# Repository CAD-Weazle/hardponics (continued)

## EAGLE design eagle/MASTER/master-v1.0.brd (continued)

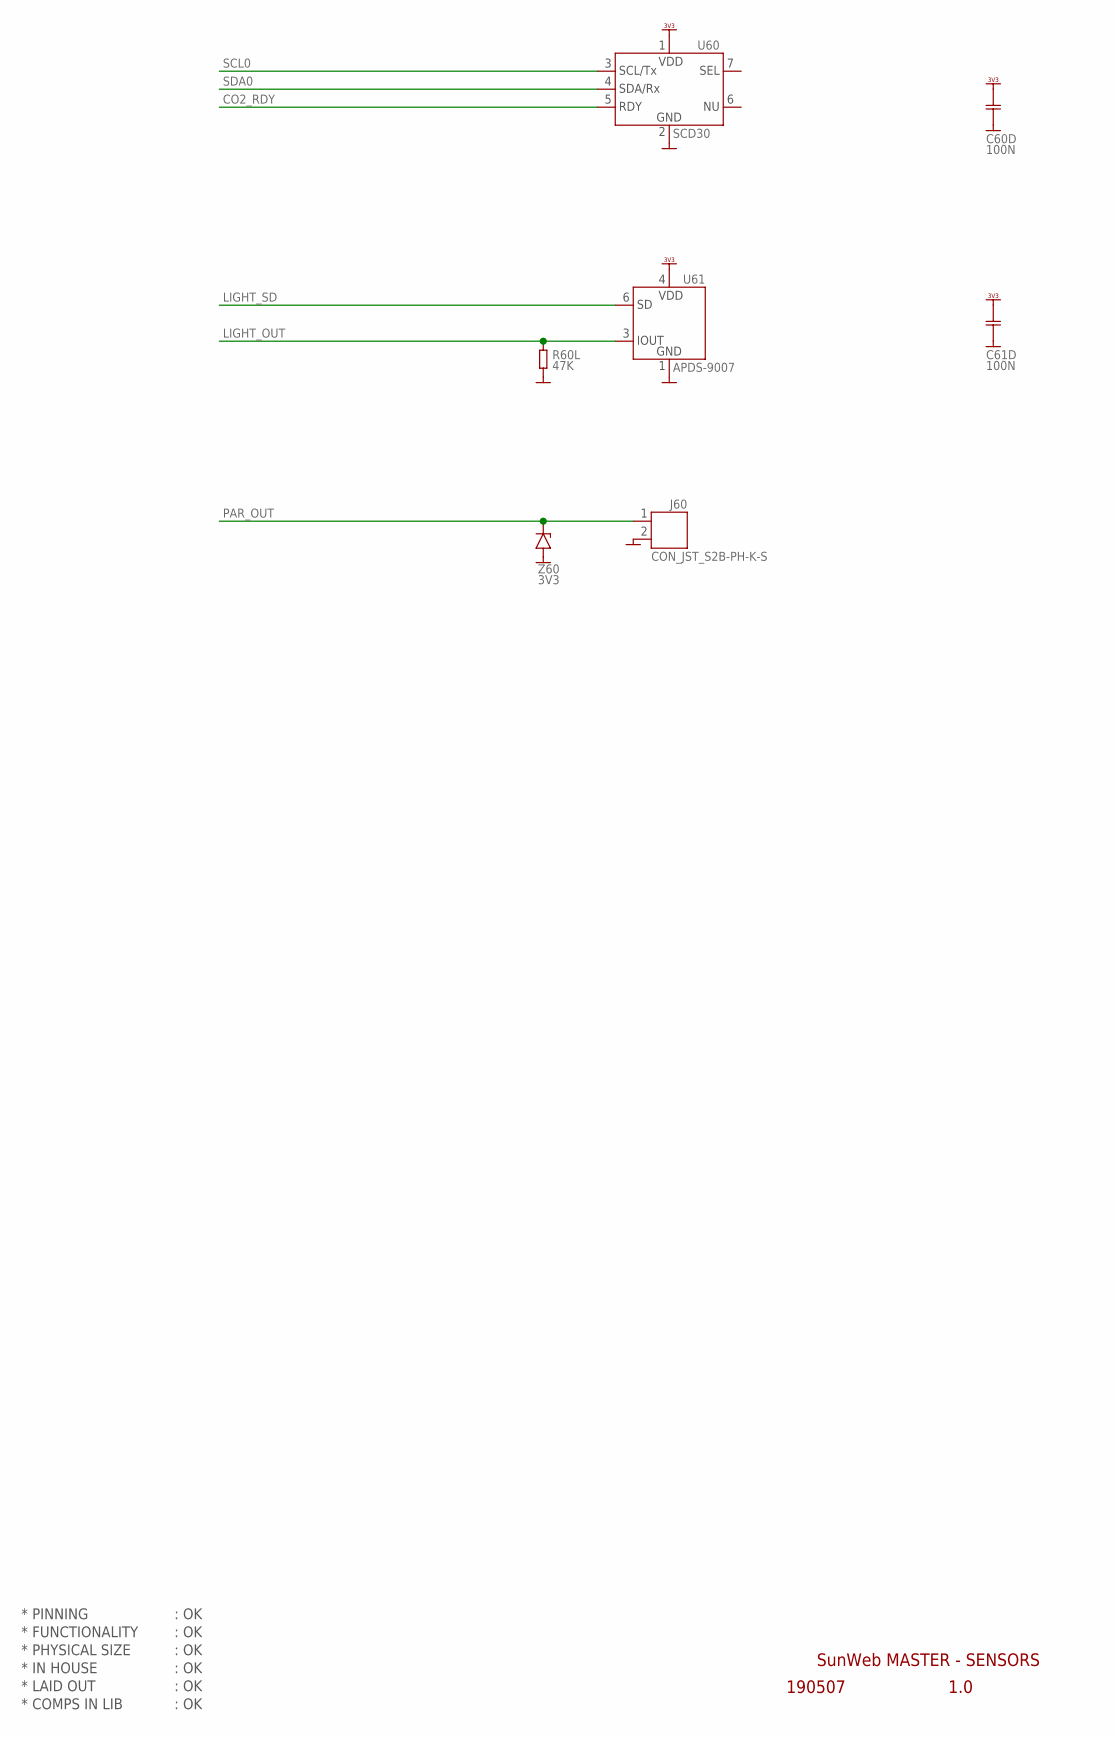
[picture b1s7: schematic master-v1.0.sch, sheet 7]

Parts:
C60D, C61D: 100N; CAP0603
J60: CON_JST_S2B-PH-K-S
R60L: 47K; RES0603
U60: SCD30
U61: APDS-9007
Z60: 3V3; ZENER_SOD80

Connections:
CO2_RDY: U60.5 (5.RDY); also elsewhere on the board
GND: C60D.2, C61D.2, J60.2, R60L.2, U60.2 (2.GND), U61.1 (1.GND), Z60.1 (+); also elsewhere on the board
LIGHT_OUT: R60L.1, U61.3 (3.IOUT); also elsewhere on the board
LIGHT_SD: U61.6 (6.SD); also elsewhere on the board
PAR_OUT: J60.1, Z60.2 (-); also elsewhere on the board
SCL0: U60.3 (3.SCL); also elsewhere on the board
SDA0: U60.4 (4.SDA); also elsewhere on the board
VDD_3V3: C60D.1, C61D.1, U60.1 (1.VDD), U61.4 (4.VDD); also elsewhere on the board

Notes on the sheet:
* PINNING
* FUNCTIONALITY
* PHYSICAL SIZE
* LAID OUT
* COMPS IN LIB
* IN HOUSE
1.0
SunWeb MASTER - SENSORS
190507
: OK

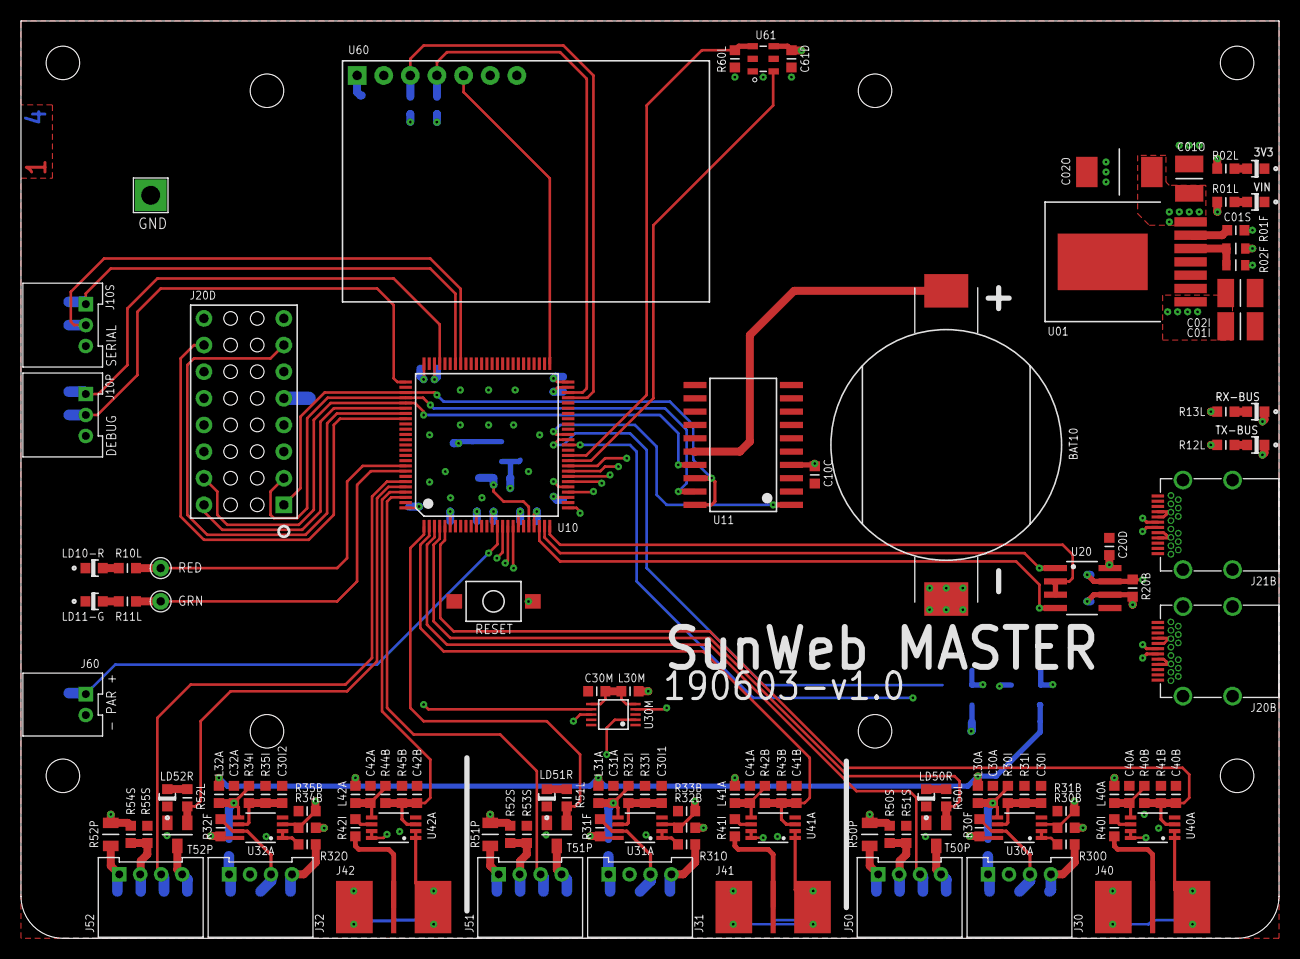
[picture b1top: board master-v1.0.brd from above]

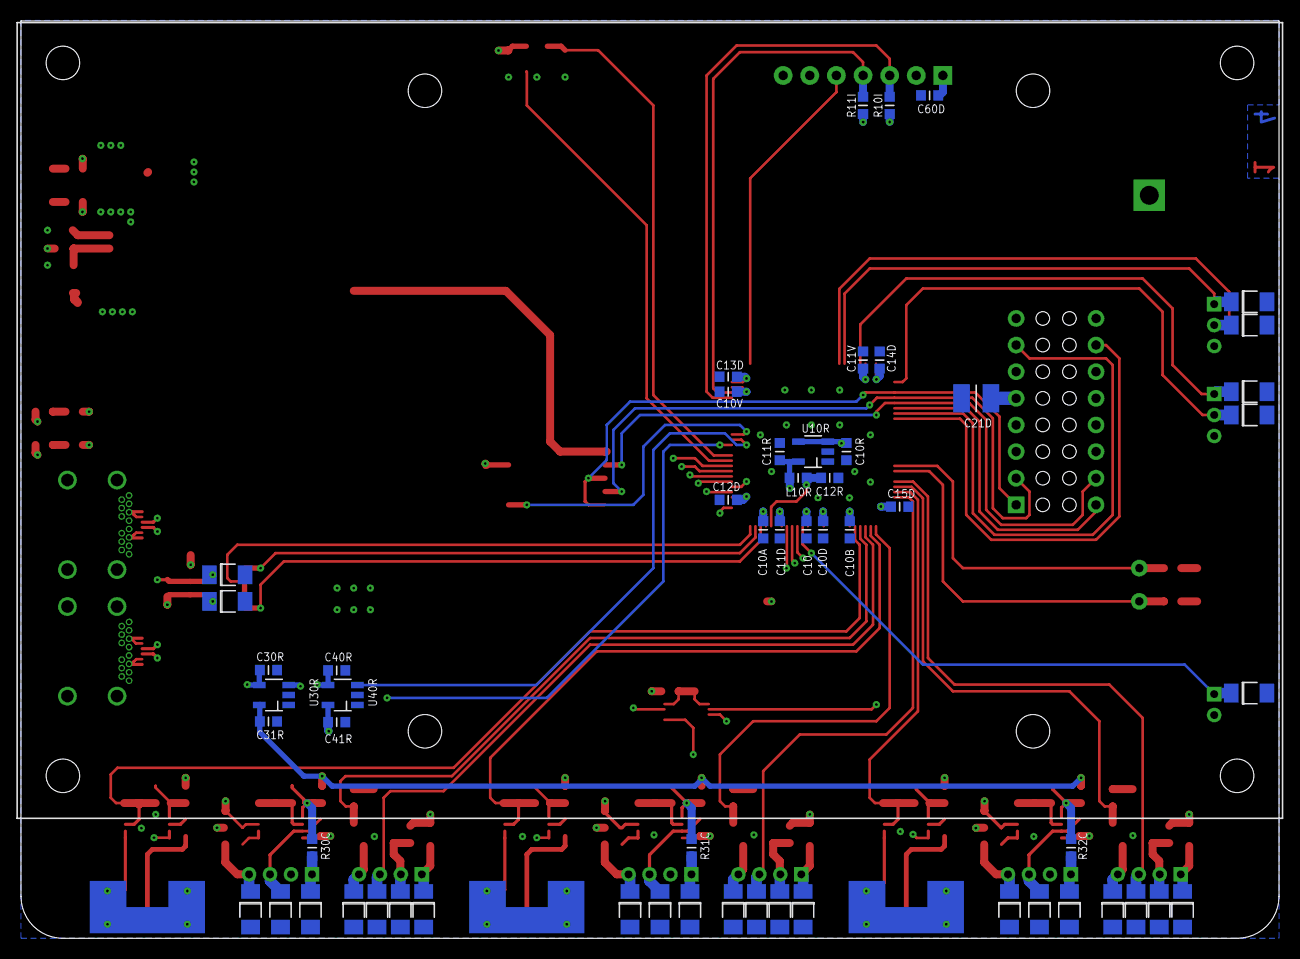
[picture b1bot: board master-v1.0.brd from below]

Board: 4 copper layers, 120.0 x 87.5 mm, 183 parts (58 on the bottom side), 107 nets.

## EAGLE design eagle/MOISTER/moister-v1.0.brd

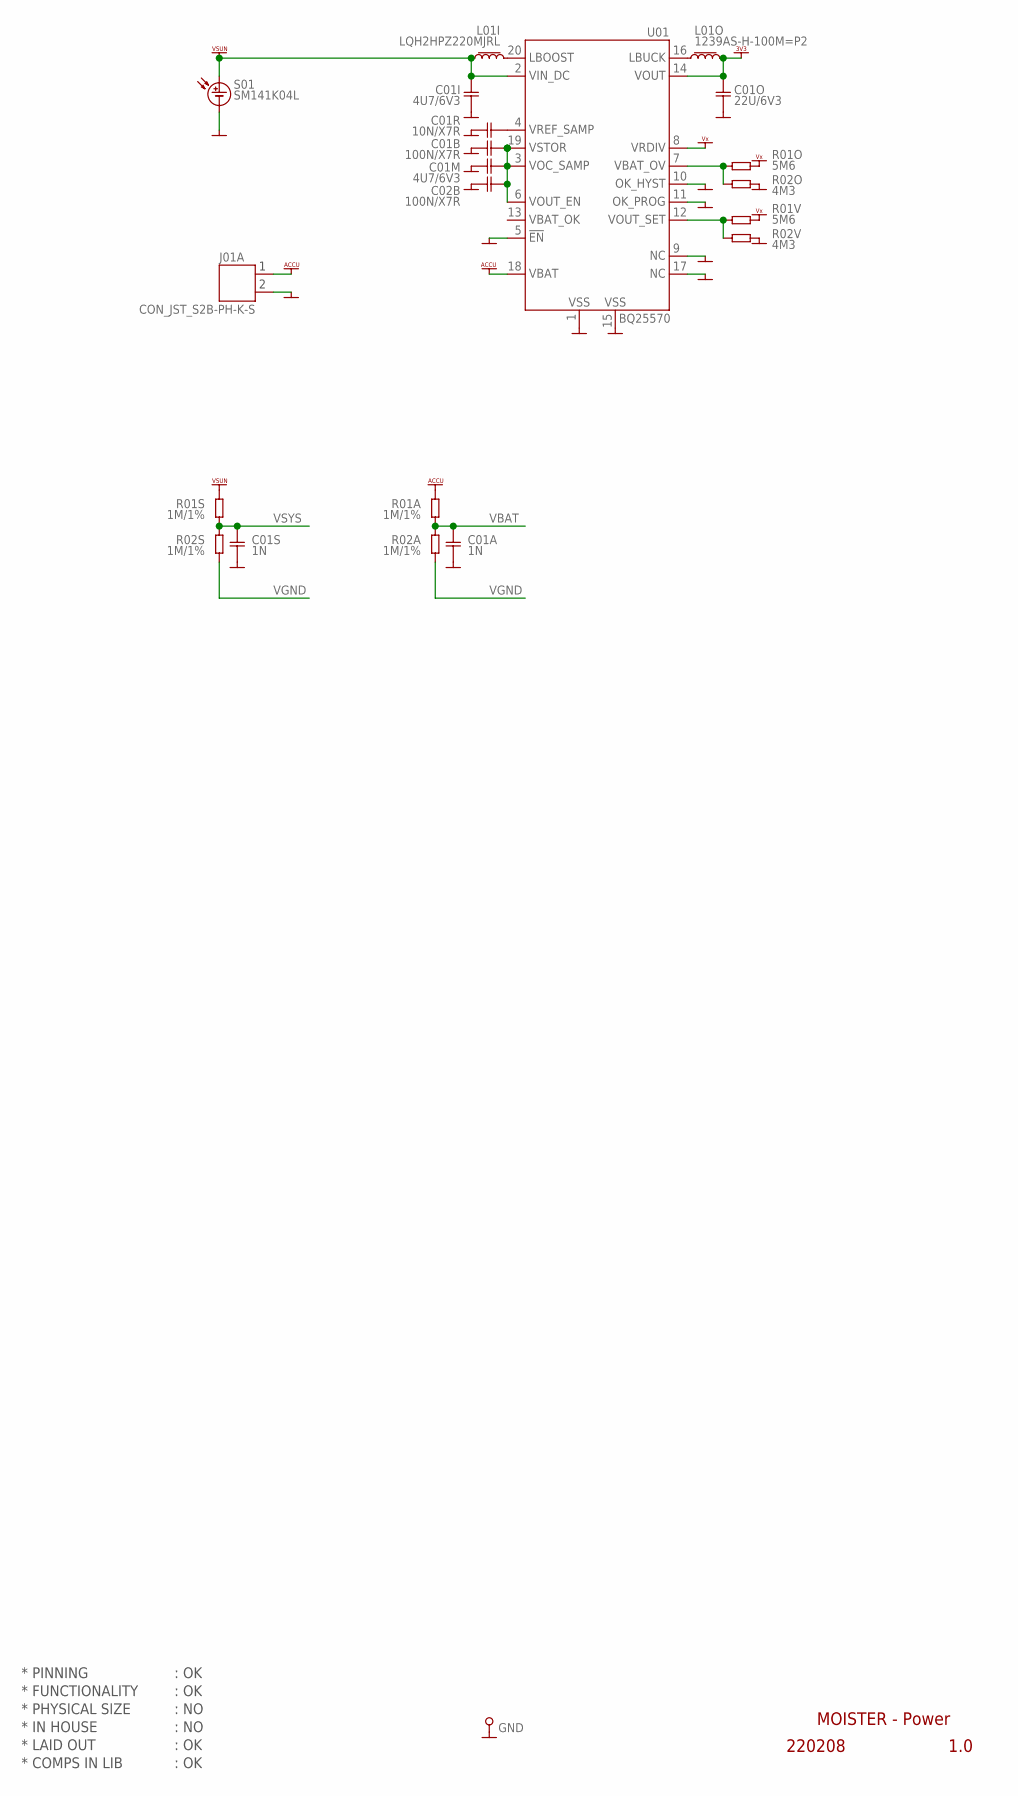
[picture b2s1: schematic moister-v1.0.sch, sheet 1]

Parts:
C01A, C01S: 1N; CAP0402
C01B, C02B: 100N/X7R; CAP0402
C01I, C01M: 4U7/6V3; CAP0402
C01O: 22U/6V3; CAP0402
C01R: 10N/X7R; CAP0402
GND: PIN_TEST; HOLE_PTH_0.8MM
J01A: CON_JST_S2B-PH-K-S
L01I: LQH2HPZ220MJRL; L_1008
L01O: 1239AS-H-100M=P2; L_1008
R01A, R01S, R02A, R02S: 1M/1%; RES0402
R01O, R01V: 5M6; RES0402
R02O, R02V: 4M3; RES0402
S01: SM141K04L
U01: BQ25570; VQFN20

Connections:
ACCU: J01A.1, R01A.2, U01.18 (18.VBAT)
GND: C01A.2, C01B.2, C01I.2, C01M.2, C01O.2, C01R.2, C01S.2, C02B.2, GND.1, J01A.2, R02O.2, R02V.2, S01.-, U01.1 (1.VSS), U01.5 (5.!EN), U01.9 (9.NC), U01.10 (10.OK_HYST), U01.11 (11.OK_PROG), U01.15 (15.VSS), U01.17 (17.NC), U01.TP (15.VSS), U01.V1 (15.VSS), U01.V2 (15.VSS), U01.V3 (15.VSS), U01.V4 (15.VSS); also elsewhere on the board
unnamed: C01R.1, U01.4 (4.VREF_SAMP)
unnamed: L01I.2, U01.20 (20.LBOOST)
unnamed: L01O.1, U01.16 (16.LBUCK)
VBAT: C01A.1, R01A.1, R02A.2; also elsewhere on the board
VBAT_OV: R01O.2, R02O.1, U01.7 (7.VBAT_OV)
VDD_3V3: C01O.1, L01O.2, U01.14 (14.VOUT); also elsewhere on the board
VGND: R02A.1, R02S.1; also elsewhere on the board
VOUT_SET: R01V.2, R02V.1, U01.12 (12.VOUT_SET)
VSTOR: C01B.1, C01M.1, C02B.1, U01.3 (3.VOC_SAMP), U01.6 (6.VOUT_EN), U01.19 (19.VSTOR)
VSUN: C01I.1, L01I.1, R01S.2, S01.+, U01.2 (2.VIN_DC)
VSYS: C01S.1, R01S.1, R02S.2; also elsewhere on the board
VX: R01O.1, R01V.1, U01.8 (8.VRDIV)

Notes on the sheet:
* PINNING
* FUNCTIONALITY
* PHYSICAL SIZE
* LAID OUT
* COMPS IN LIB
* IN HOUSE
MOISTER - Power
220208
1.0
: OK
: NO

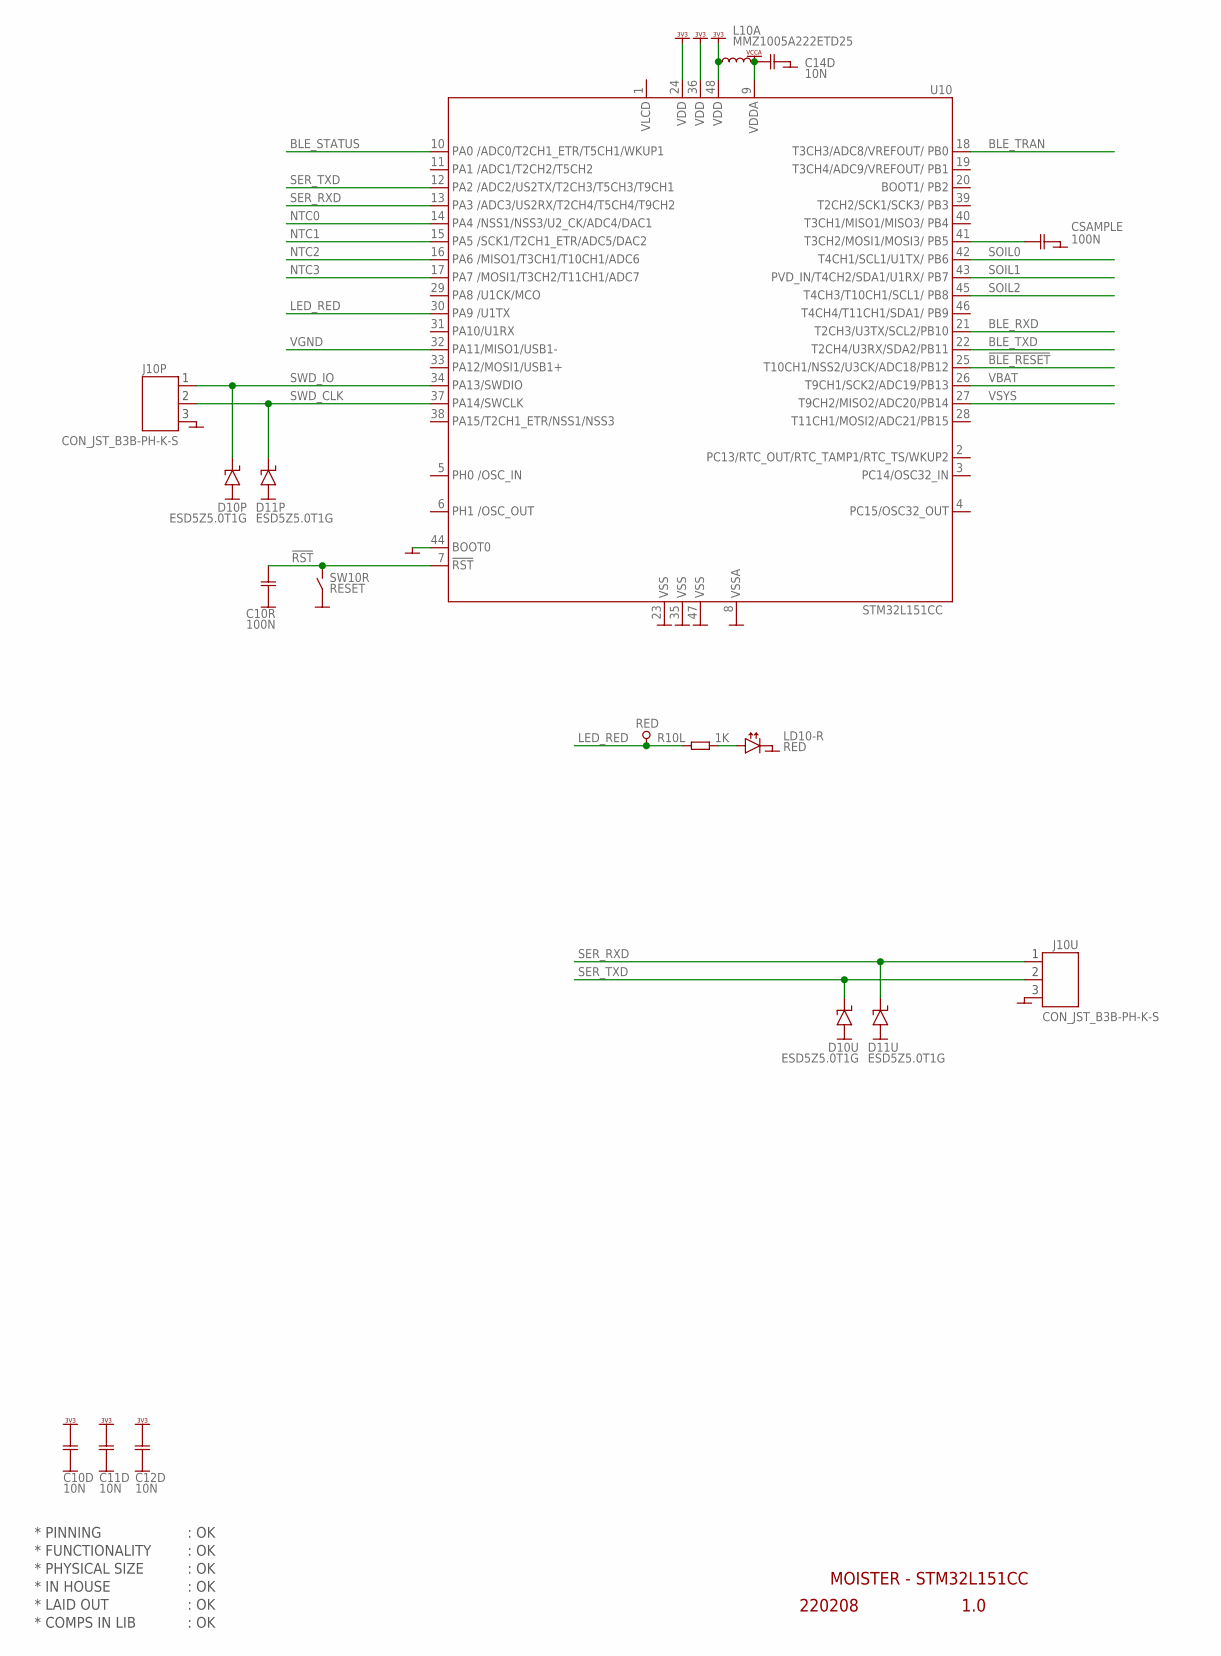
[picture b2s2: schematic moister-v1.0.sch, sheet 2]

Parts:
C10D, C11D, C12D, C14D: 10N; CAP0402
C10R: 100N; CAP0402
CSAMPLE: 100N; CAP0603
D10P, D10U, D11P, D11U: ESD5Z5.0T1G; DIODE_SOD523
J10P, J10U: CON_JST_B3B-PH-K-S
L10A: MMZ1005A222ETD25; L_0402
LD10-R: RED; LED_SMD_0402
R10L: 1K; RES0402
RED: PIN_TEST_0.6MM; HOLE_PTH_0.6MM
SW10R: RESET; SWITCH_SMD_PBUTTON_2P
U10: STM32L151CC; LQFP48

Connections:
!BLE_RESET: U10.25 (25.PB12); also elsewhere on the board
!RST: C10R.1, SW10R.1 (1-2), U10.7 (7.!RST)
BLE_RXD: U10.21 (21.PB10); also elsewhere on the board
BLE_STATUS: U10.10 (10.PA0); also elsewhere on the board
BLE_TRAN: U10.18 (18.PB0); also elsewhere on the board
BLE_TXD: U10.22 (22.PB11); also elsewhere on the board
CSAMPLE: CSAMPLE.1, U10.41 (41.PB5)
GND: C10D.2, C10R.2, C11D.2, C12D.2, C14D.2, CSAMPLE.2, D10P.A, D10U.A, D11P.A, D11U.A, J10P.3, J10U.3, LD10-R.C, SW10R.2 (3-4), U10.8 (8.GND), U10.23 (23.GND), U10.35 (35.GND), U10.44 (44.BOOT0), U10.47 (47.GND); also elsewhere on the board
LED_RED: R10L.1, RED.1, U10.30 (30.PA9)
unnamed: LD10-R.A, R10L.2
NTC0: U10.14 (14.PA4); also elsewhere on the board
NTC1: U10.15 (15.PA5); also elsewhere on the board
NTC2: U10.16 (16.PA6); also elsewhere on the board
NTC3: U10.17 (17.PA7); also elsewhere on the board
SER_RXD: D11U.C, J10U.1, U10.13 (13.PA3)
SER_TXD: D10U.C, J10U.2, U10.12 (12.PA2)
SOIL0: U10.42 (42.PB6); also elsewhere on the board
SOIL1: U10.43 (43.PB7); also elsewhere on the board
SOIL2: U10.45 (45.PB8); also elsewhere on the board
SWD_CLK: D11P.C, J10P.2, U10.37 (37.PA14)
SWD_IO: D10P.C, J10P.1, U10.34 (34.PA13)
VBAT: U10.26 (26.PB13); also elsewhere on the board
VCCA: C14D.1, L10A.2, U10.9 (9.VDD); also elsewhere on the board
VDD_3V3: C10D.1, C11D.1, C12D.1, L10A.1, U10.24 (24.VDD), U10.36 (36.VDD), U10.48 (48.VDD); also elsewhere on the board
VGND: U10.32 (32.PA11); also elsewhere on the board
VSYS: U10.27 (27.PB14); also elsewhere on the board

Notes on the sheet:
* PINNING
* FUNCTIONALITY
* PHYSICAL SIZE
* LAID OUT
* COMPS IN LIB
* IN HOUSE
: OK
MOISTER - STM32L151CC
220208
1.0

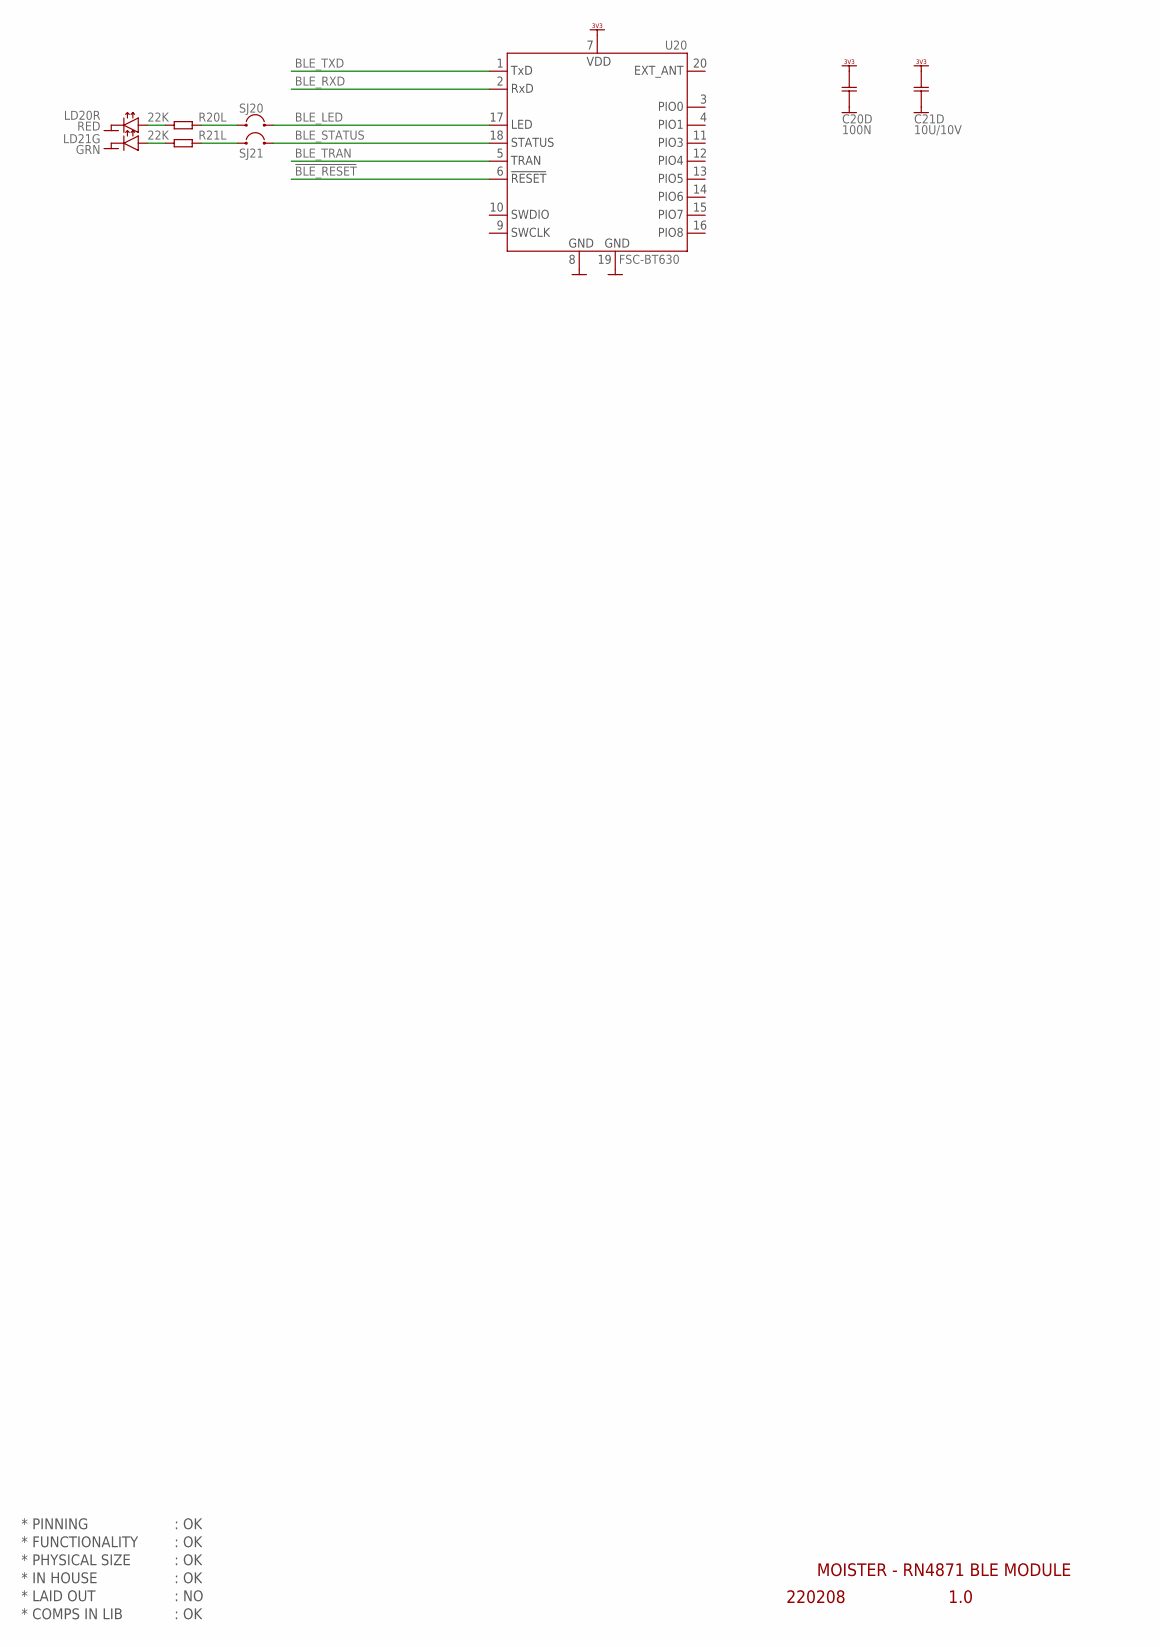
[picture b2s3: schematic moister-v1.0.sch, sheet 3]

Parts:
C20D: 100N; CAP0402
C21D: 10U/10V; CAP0402
LD20R: RED; LED_SMD_0402
LD21G: GRN; LED_SMD_0402
R20L, R21L: 22K; RES0402
SJ20, SJ21: SJ2SJ2-S; SJ2-S
U20: FSC-BT630

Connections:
!BLE_RESET: U20.6 (6.!RESET); also elsewhere on the board
BLE_LED: SJ20.2, U20.17 (17.LED)
BLE_RXD: U20.2 (2.RXD); also elsewhere on the board
BLE_STATUS: SJ21.2, U20.18 (18.STATUS); also elsewhere on the board
BLE_TRAN: U20.5 (5.TRAN); also elsewhere on the board
BLE_TXD: U20.1 (1.TXD); also elsewhere on the board
GND: C20D.2, C21D.2, LD20R.C, LD21G.C, U20.8 (8.GND), U20.19 (19.GND); also elsewhere on the board
unnamed: LD20R.A, R20L.2
unnamed: R20L.1, SJ20.1
unnamed: R21L.1, SJ21.1
unnamed: LD21G.A, R21L.2
VDD_3V3: C20D.1, C21D.1, U20.7 (7.VDD); also elsewhere on the board

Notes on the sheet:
* PINNING
* FUNCTIONALITY
* PHYSICAL SIZE
* LAID OUT
* COMPS IN LIB
* IN HOUSE
1.0
MOISTER - RN4871 BLE MODULE
220208
: OK
: NO

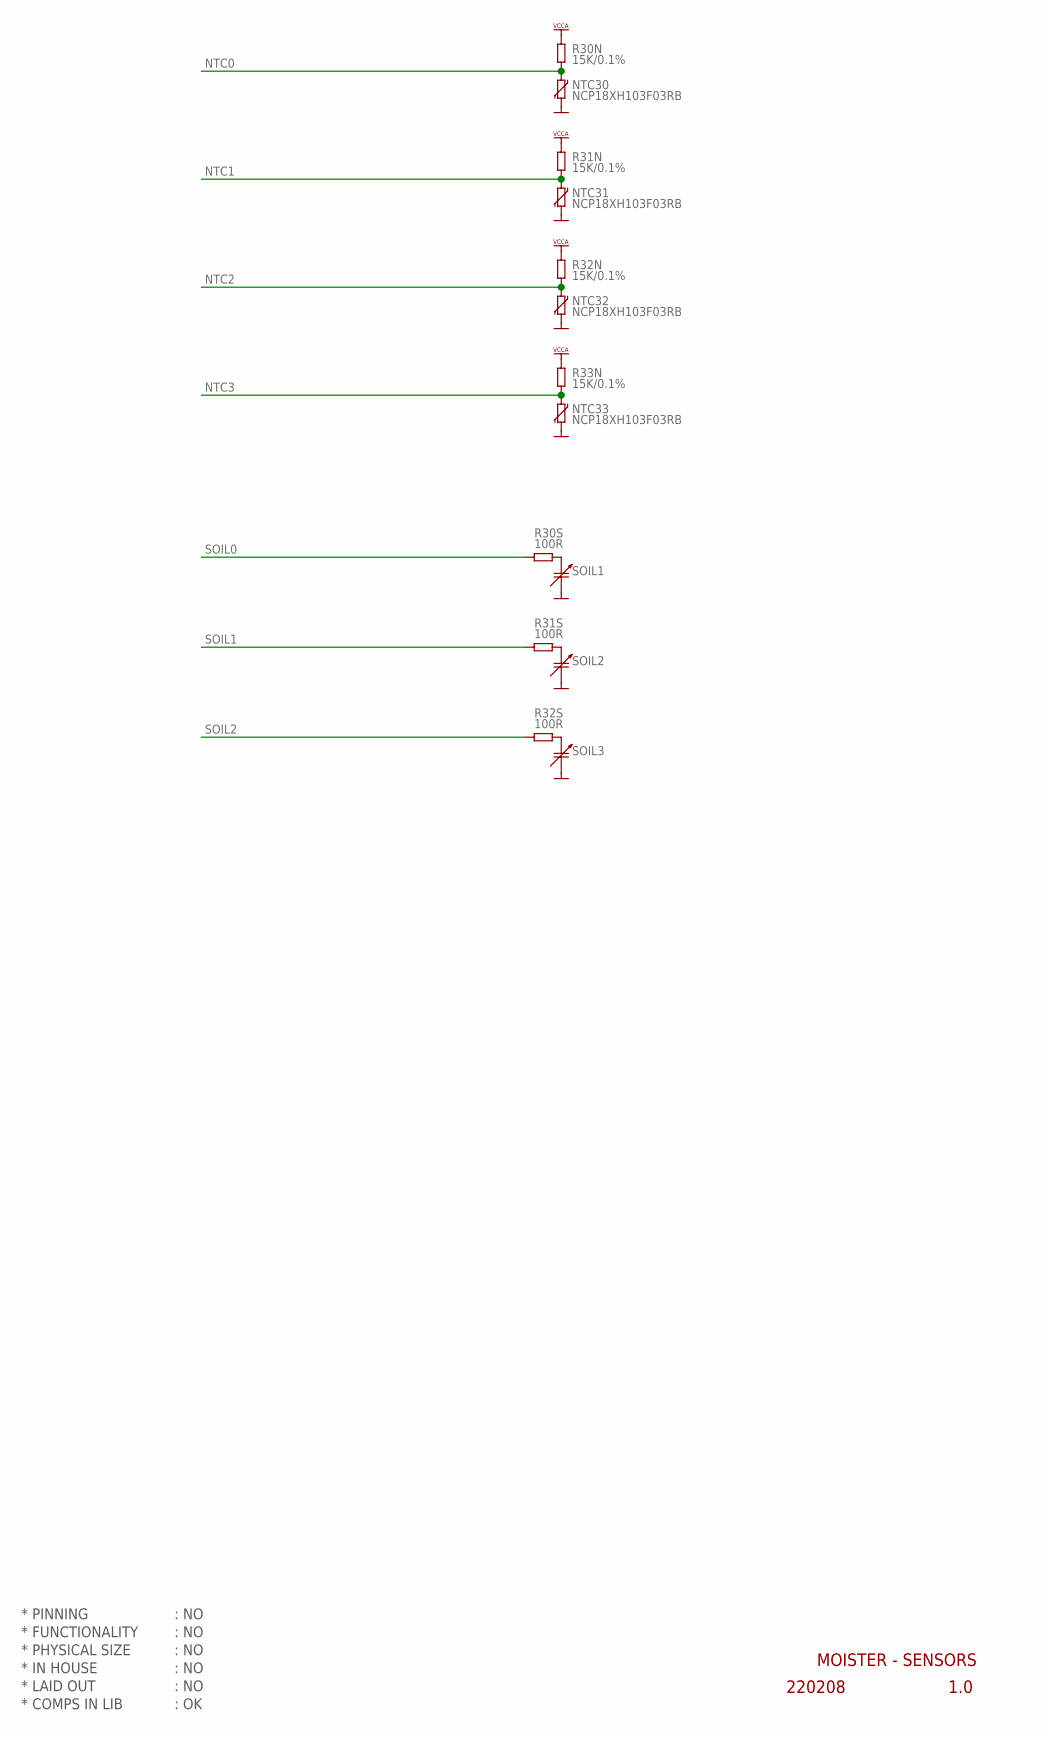
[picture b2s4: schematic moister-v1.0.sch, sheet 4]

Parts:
NTC30, NTC31, NTC32, NTC33: NCP18XH103F03RB; RES0603
R30N, R31N, R32N, R33N: 15K/0.1%; RES0402
R30S, R31S, R32S: 100R; RES0402
SOIL1, SOIL2, SOIL3: CAP_SOIL_SINGLE_2LAYER

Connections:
GND: NTC30.1, NTC31.1, NTC32.1, NTC33.1, SOIL1.2, SOIL2.2, SOIL3.2; also elsewhere on the board
unnamed: R30S.2, SOIL1.1
unnamed: R31S.2, SOIL2.1
unnamed: R32S.2, SOIL3.1
NTC0: NTC30.2, R30N.2; also elsewhere on the board
NTC1: NTC31.2, R31N.2; also elsewhere on the board
NTC2: NTC32.2, R32N.2; also elsewhere on the board
NTC3: NTC33.2, R33N.2; also elsewhere on the board
SOIL0: R30S.1; also elsewhere on the board
SOIL1: R31S.1; also elsewhere on the board
SOIL2: R32S.1; also elsewhere on the board
VCCA: R30N.1, R31N.1, R32N.1, R33N.1; also elsewhere on the board

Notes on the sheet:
* PINNING
* FUNCTIONALITY
* PHYSICAL SIZE
* LAID OUT
* COMPS IN LIB
* IN HOUSE
1.0
MOISTER - SENSORS
220208
: NO
: OK

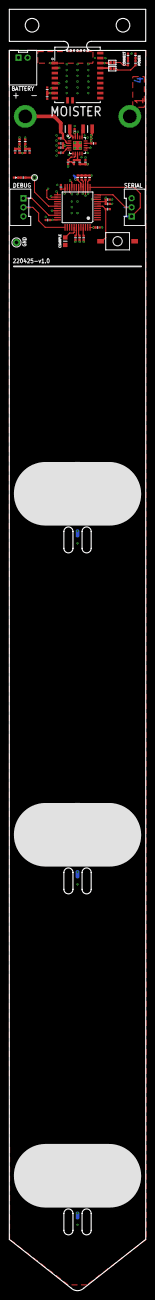
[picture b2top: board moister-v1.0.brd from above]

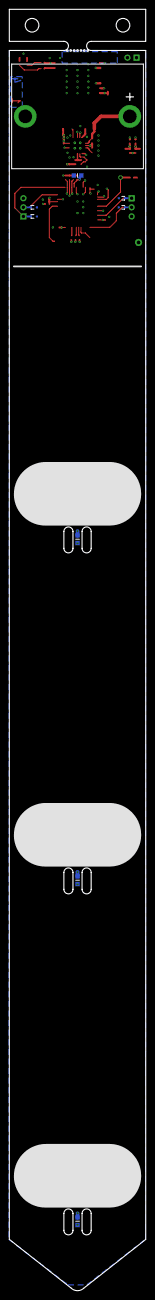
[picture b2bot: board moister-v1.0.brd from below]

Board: 4 copper layers, 30.0 x 281.8 mm, 66 parts (9 on the bottom side), 43 nets.

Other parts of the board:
U$45: EC_MOUSEBITES
U$46, U$47: EC_TOOL-REGISTRATION

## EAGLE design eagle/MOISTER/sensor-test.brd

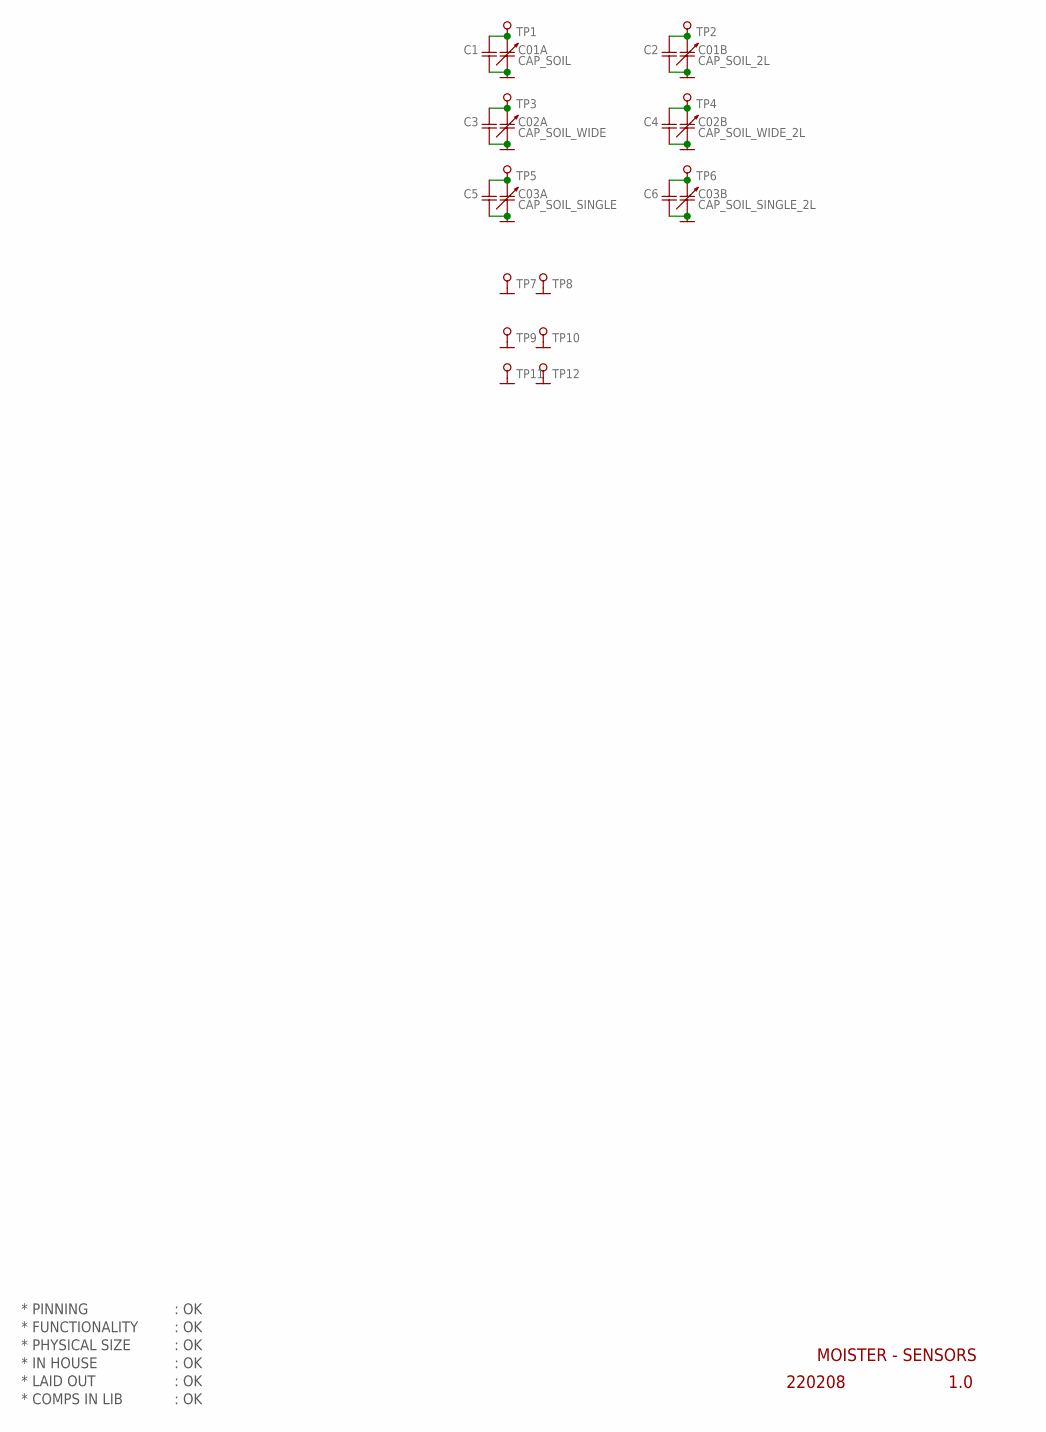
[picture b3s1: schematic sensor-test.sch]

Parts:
C1, C2, C3, C4, C5, C6: CAP0805
C01A: CAP_SOIL
C01B: CAP_SOIL_2L; CAP_SOIL_2LAYER
C02A: CAP_SOIL_WIDE
C02B: CAP_SOIL_WIDE_2L; CAP_SOIL_WIDE_2LAYER
C03A: CAP_SOIL_SINGLE
C03B: CAP_SOIL_SINGLE_2L; CAP_SOIL_SINGLE_2LAYER
TP1, TP2, TP3, TP4, TP5, TP6, TP7, TP8, TP9, TP10, TP11, TP12: PIN_TEST; HOLE_PTH_0.8MM

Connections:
GND: C1.2, C01A.2, C01B.2, C01B.P$1 (2), C2.2, C02A.2, C02B.2, C02B.P$1 (2), C3.2, C03A.2, C03B.2, C4.2, C5.2, C6.2, TP7.1, TP8.1, TP9.1, TP10.1, TP11.1, TP12.1
unnamed: C1.1, C01A.1, TP1.1
unnamed: C01B.1, C2.1, TP2.1
unnamed: C02A.1, C3.1, TP3.1
unnamed: C02B.1, C4.1, TP4.1
unnamed: C03A.1, C5.1, TP5.1
unnamed: C03B.1, C6.1, TP6.1

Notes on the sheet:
* PINNING
* FUNCTIONALITY
* PHYSICAL SIZE
* LAID OUT
* COMPS IN LIB
* IN HOUSE
1.0
MOISTER - SENSORS
220208
: OK

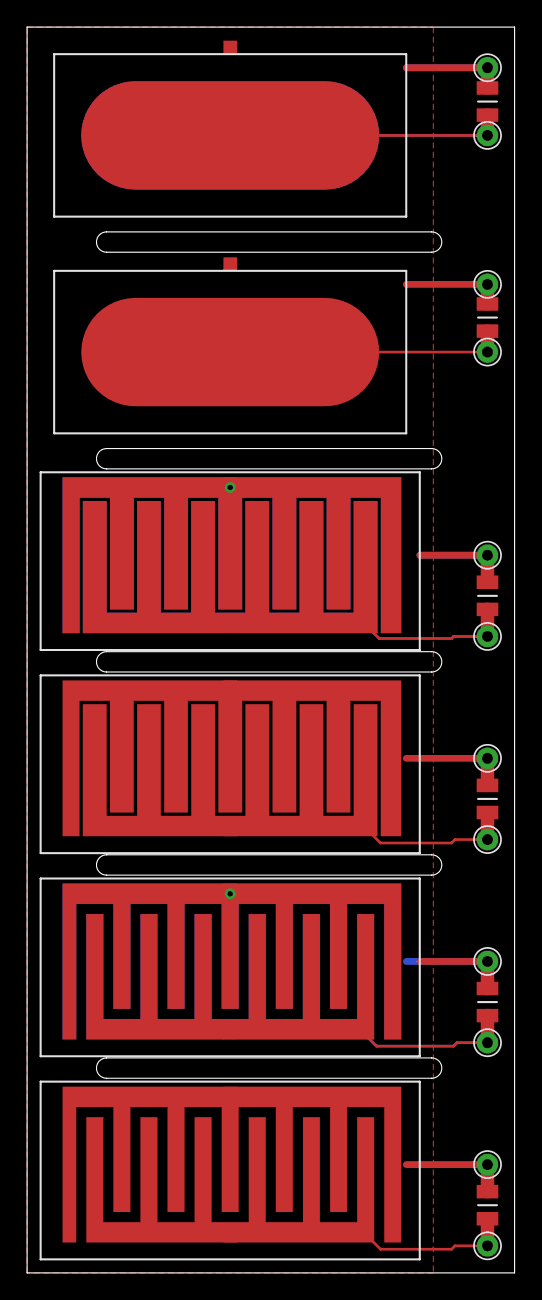
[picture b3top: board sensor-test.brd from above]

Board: 4 copper layers, 36.0 x 92.0 mm, 24 parts (0 on the bottom side), 7 nets.

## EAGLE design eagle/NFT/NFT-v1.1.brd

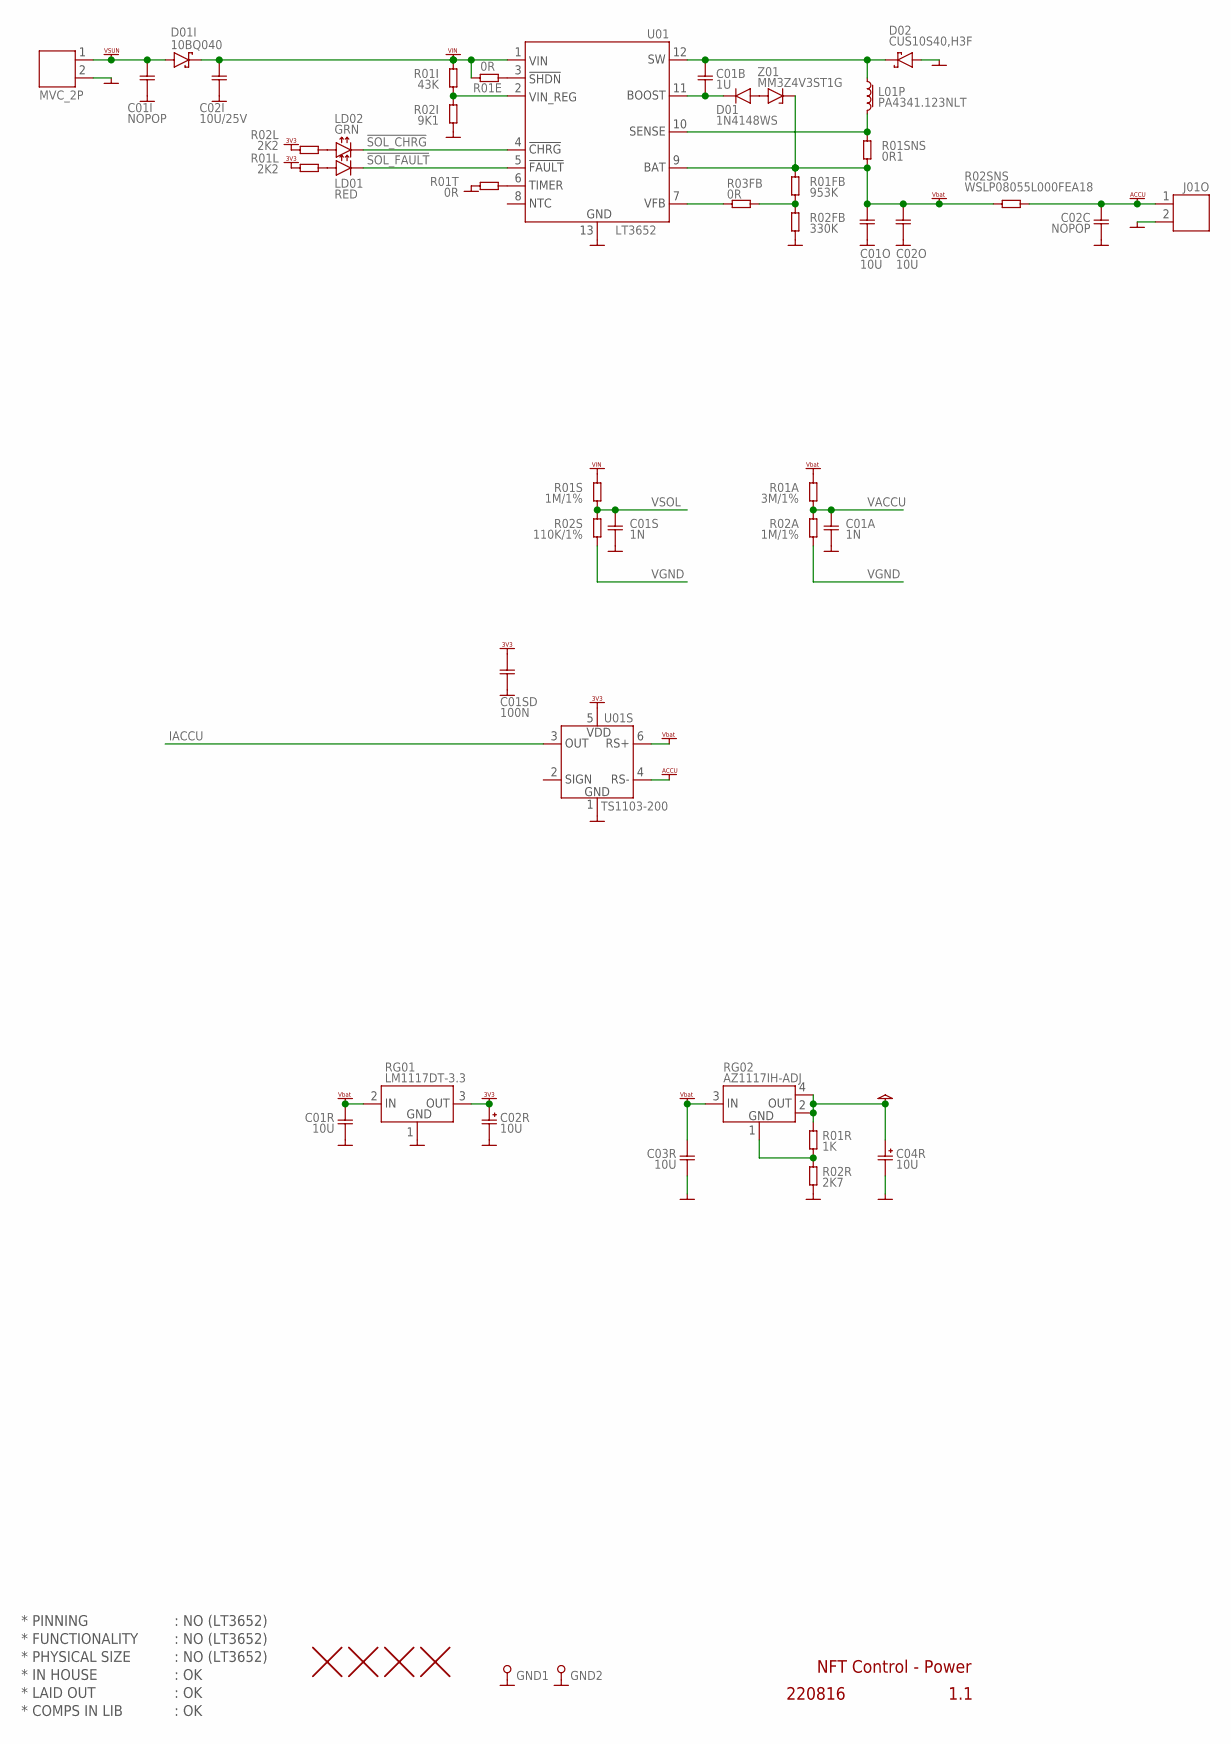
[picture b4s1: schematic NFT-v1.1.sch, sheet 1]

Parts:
C01A, C01S: 1N; CAP0402
C01B: 1U; CAP0402
C01I, C02C: NOPOP; CAP1812
C01O, C02O: 10U; CAP0805
C01R, C03R: 10U; CAP0603
C01SD: 100N; CAP0402
C02I: 10U/25V; CAP0805
C02R, C04R: 10U; ECAP_SMA
D01: 1N4148WS; DIODE_SOD323
D01I: 10BQ040; DIODE_SMB
D02: CUS10S40,H3F; DIODE_SOD323
GND1, GND2: PIN_TEST; HOLE_PTH_0.8MM
H1, H2, H3, H4: HOLE_NPTH_3.2MM
J01I: MVC_2P; CON_PHOENIX_COMBICON_MCV_HEADER_P
J01O: CON_PHOENIX_COMBICON_MCV_HEADER_2P; CON_PHOENIX_COMBICON_MCV_HEADER_P
L01P: PA4341.123NLT; L_PA4341
LD01: RED; LED_SMD_0402
LD02: GRN; LED_SMD_0402
R01A: 3M/1%; RES0402
R01E, R01T, R03FB: 0R; RES0402
R01FB: 953K; RES0402
R01I: 43K; RES0402
R01L, R02L: 2K2; RES0402
R01R: 1K; RES0402
R01S, R02A: 1M/1%; RES0402
R01SNS: 0R1; RES0603
R02FB: 330K; RES0402
R02I: 9K1; RES0402
R02R: 2K7; RES0402
R02S: 110K/1%; RES0402
R02SNS: WSLP08055L000FEA18; RES0805
RG01: LM1117DT-3.3; TO252
RG02: AZ1117IH-ADJ; SOT223
U01: LT3652; MSOP-12_GND
U01S: TS1103-200; SOT23-6
Z01: MM3Z4V3ST1G; ZENER_SOD323

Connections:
!SOL_CHRG: LD02.C, U01.4 (4.!CHRG); also elsewhere on the board
!SOL_FAULT: LD01.C, U01.5 (5.!FAULT)
ACCU: C02C.1, J01O.1, R02SNS.2, U01S.4 (4.RS-)
BOOST: C01B.2, D01.C (-), U01.11 (11.BOOST)
FB1: R01R.2, R02R.1, RG02.1 (1.GND)
GND: C01A.2, C01I.2, C01O.2, C01R.2, C01S.2, C01SD.2, C02C.2, C02I.2, C02O.2, C02R.-, C03R.2, C04R.-, D02.A, GND1.1, GND2.1, J01I.2, J01O.2, R01T.2, R02FB.1, R02I.1, R02R.2, RG01.1 (1.GND), U01.13 (GND_PAD), U01S.1 (1.GND); also elsewhere on the board
IACCU: U01S.3 (3.OUT); also elsewhere on the board
unnamed: R03FB.2, U01.7 (7.VFB)
unnamed: LD01.A, R01L.2
unnamed: LD02.A, R02L.2
unnamed: R01T.1, U01.6 (6.TIMER)
unnamed: D01.A (+), Z01.A
unnamed: R01E.1, U01.3 (3.!SHDN)
SENSE: L01P.P$2 (2), R01SNS.2, U01.10 (10.SENSE)
SW: C01B.1, D02.C, L01P.P$1 (1), U01.12 (12.SW)
VACCU: C01A.1, R01A.1, R02A.2; also elsewhere on the board
VBAT: C01O.1, C01R.1, C02O.1, C03R.1, R01A.2, R01FB.2, R01SNS.1, R02SNS.1, RG01.2 (2.IN), RG02.3 (3.IN), U01.9 (9.BAT), U01S.6 (6.RS+), Z01.C; also elsewhere on the board
VCC: C04R.+, R01R.1, RG02.2 (2.OUT), RG02.4 (4.OUT); also elsewhere on the board
VDD_3V3: C01SD.1, C02R.+, R01L.1, R02L.1, RG01.3 (3.OUT), U01S.5 (5.VDD); also elsewhere on the board
VFB: R01FB.1, R02FB.2, R03FB.1
VGND: R02A.1, R02S.1; also elsewhere on the board
VIN: C02I.1, D01I.C (-), R01E.2, R01I.2, R01S.2, U01.1 (1.VIN)
VIN_REG: R01I.1, R02I.2, U01.2 (2.VIN_REG)
VSOL: C01S.1, R01S.1, R02S.2; also elsewhere on the board
VSUN: C01I.1, D01I.A (+), J01I.1

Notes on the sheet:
* PINNING
* FUNCTIONALITY
* PHYSICAL SIZE
* LAID OUT
* COMPS IN LIB
* IN HOUSE
NFT Control - Power
220816
1.1
: NO (LT3652)
: OK
